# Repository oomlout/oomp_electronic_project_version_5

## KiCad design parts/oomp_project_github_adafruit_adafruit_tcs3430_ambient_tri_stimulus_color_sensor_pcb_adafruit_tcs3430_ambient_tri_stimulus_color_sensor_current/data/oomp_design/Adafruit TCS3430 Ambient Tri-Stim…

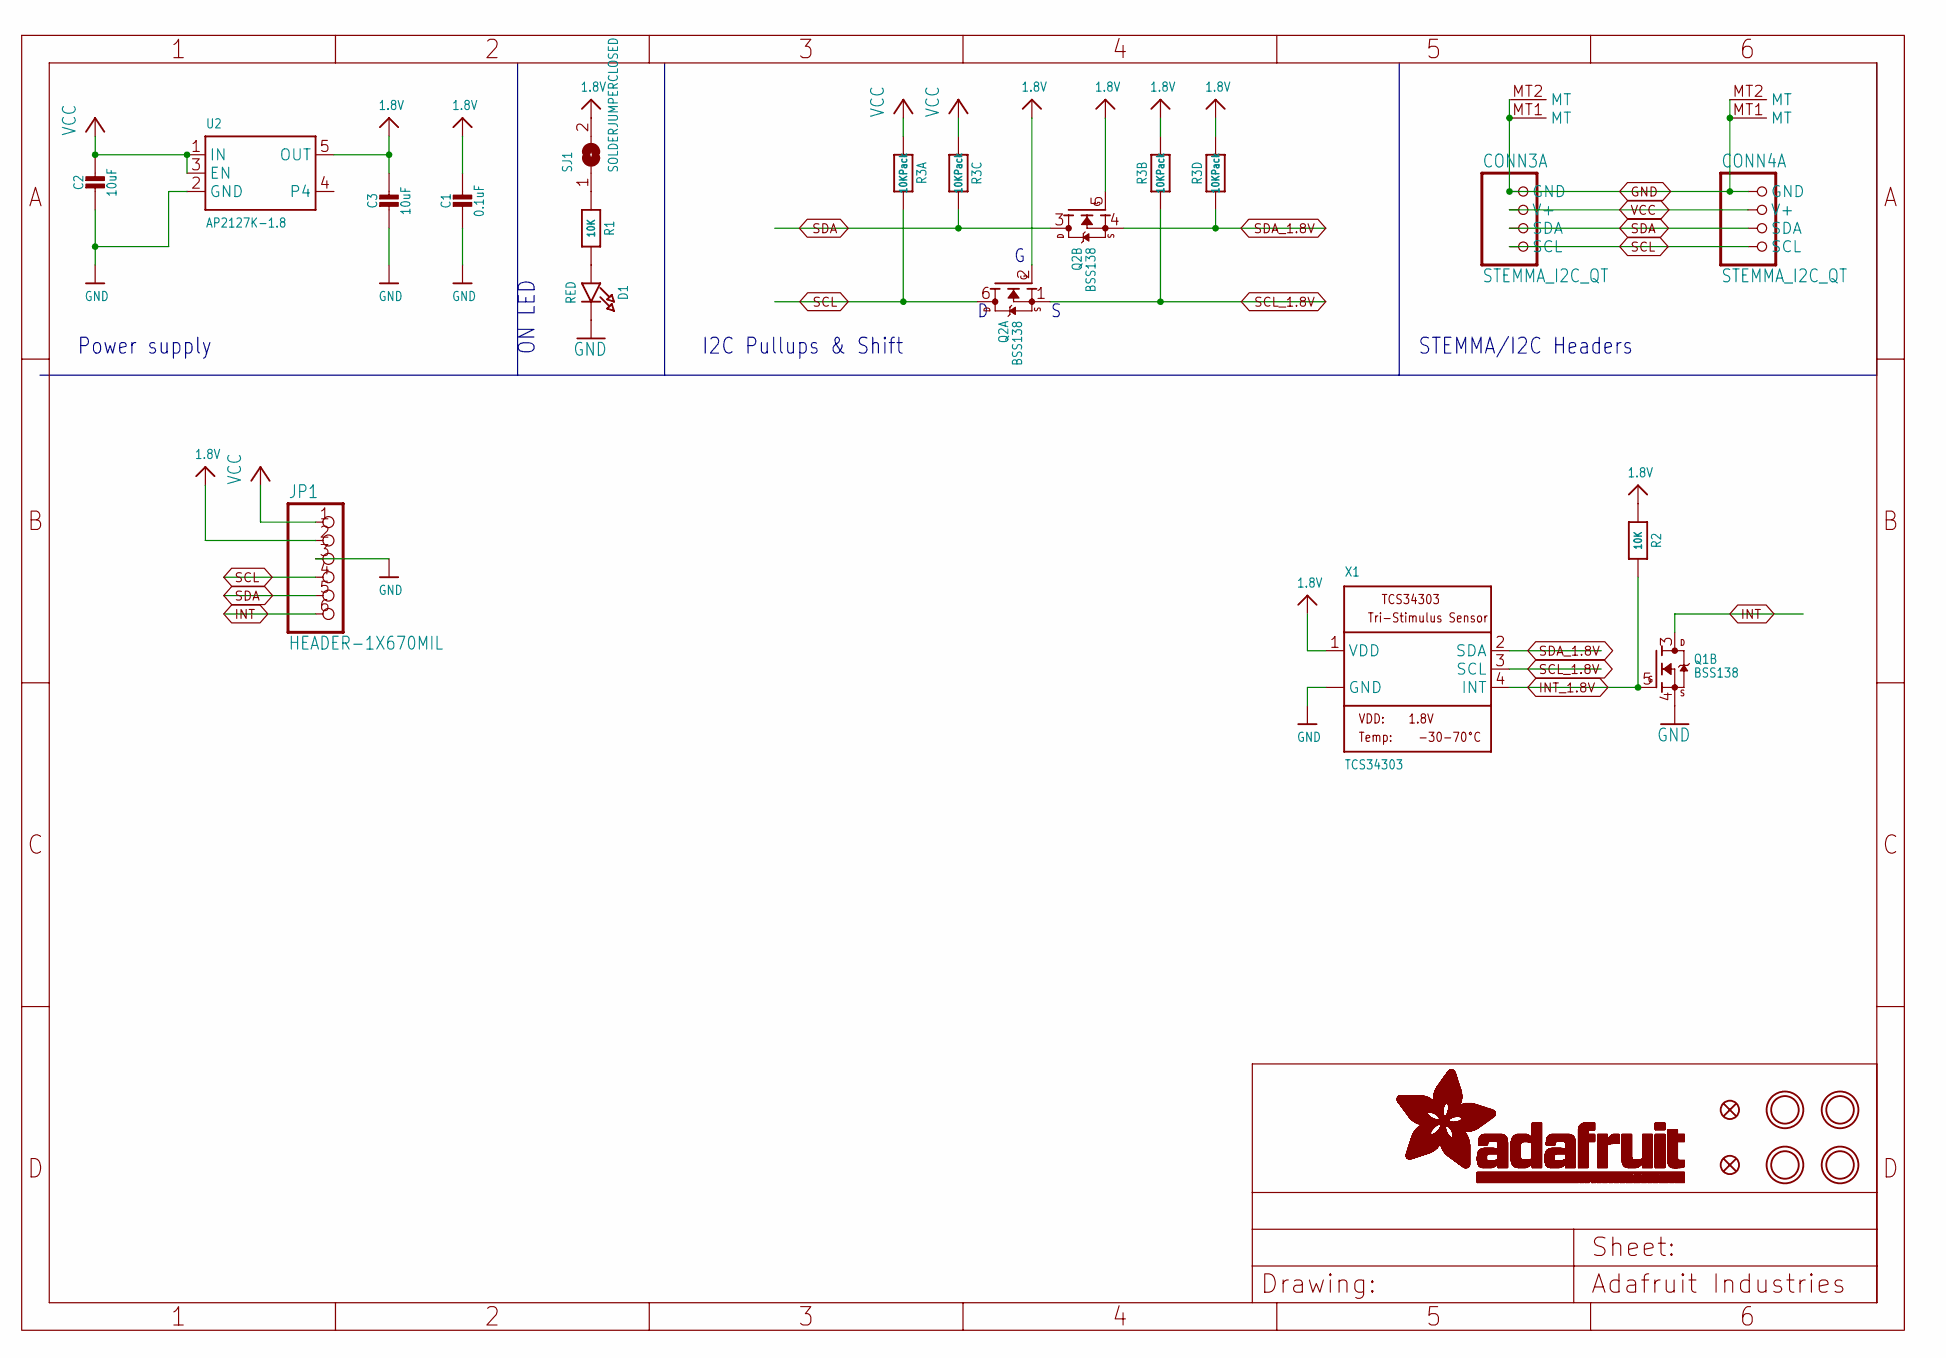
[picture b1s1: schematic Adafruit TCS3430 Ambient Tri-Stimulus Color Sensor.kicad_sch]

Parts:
C1: 0.1uF; 0603-NO
C2, C3: 10uF; 0805-NO
CONN3, CONN4: STEMMA_I2C_QT; JST_SH4; LCSC C2845363
D1: RED; CHIPLED_0603_NOOUTLINE; JLC_ROTATION 270
FID3, FID4: FIDUCIAL_0.5MM
JP1: HEADER-1X670MIL; 1X06_ROUND_70
Q1, Q2: BSS138; SOT363; JLC_ROTATION 270
R1, R2: 10K; 0603-NO
R3: 10KPack; RESPACK_4X0603
SJ1: SOLDERJUMPERCLOSED; SOLDERJUMPER_CLOSEDWIRE
U2: AP2127K-1.8; SOT23-5; JLC_ROTATION 270
U$1, U$9, U$17, U$20: MOUNTINGHOLE2.5; MOUNTINGHOLE_2.5_PLATED
X1: TCS34303

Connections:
1.8V: C1.1, C3.1, JP1.2, Q2.2 (G), Q2.5 (G), R2.1, R3.2 (1), R3.4 (1), SJ1.2, U2.5 (OUT), X1.1 (VDD)
GND: C1.2, C2.2, C3.2, CONN3.1 (GND), CONN3.MT1 (MT), CONN3.MT2 (MT), CONN4.1 (GND), CONN4.MT1 (MT), CONN4.MT2 (MT), D1.C, JP1.3, Q1.4 (S), U2.2 (GND), X1.7 (GND), X1.8 (GND)
INT: JP1.6, Q1.3 (D)
INT_1.8V: Q1.5 (G), R2.2, X1.4 (INT)
unnamed: D1.A, R1.2
unnamed: R1.1, SJ1.1
SCL: CONN3.4 (SCL), CONN4.4 (SCL), JP1.4, Q2.6 (D), R3.8 (2)
SCL_1.8V: Q2.1 (S), R3.7 (2), X1.3 (SCL)
SDA: CONN3.3 (SDA), CONN4.3 (SDA), JP1.5, Q2.3 (D), R3.6 (2)
SDA_1.8V: Q2.4 (S), R3.5 (2), X1.2 (SDA)
VCC: C2.1, CONN3.2 (V+), CONN4.2 (V+), JP1.1, R3.1, R3.3 (1), U2.1 (IN), U2.3 (EN)

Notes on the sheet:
Power supply
ON LED
STEMMA/I2C Headers
I2C Pullups & Shift

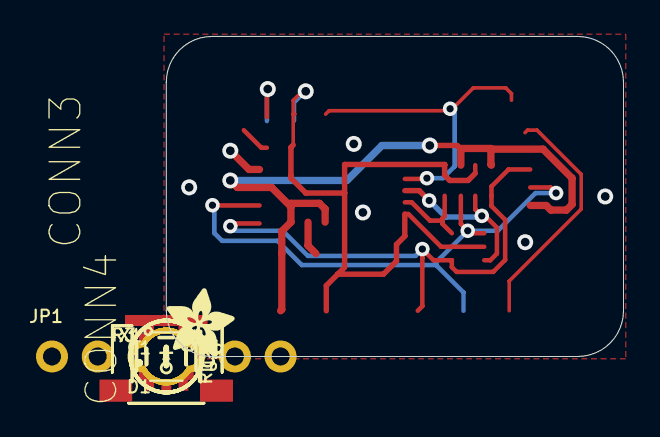
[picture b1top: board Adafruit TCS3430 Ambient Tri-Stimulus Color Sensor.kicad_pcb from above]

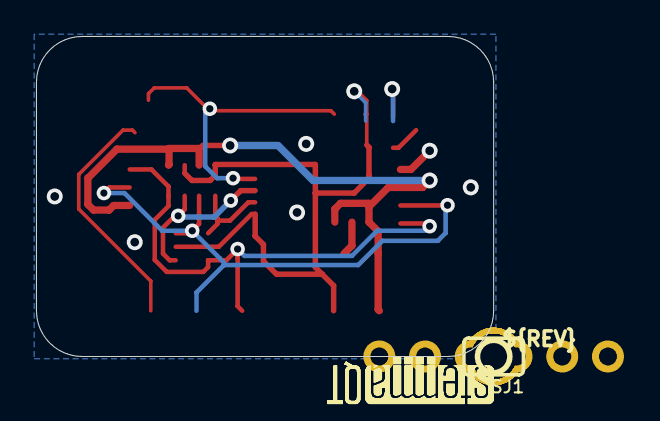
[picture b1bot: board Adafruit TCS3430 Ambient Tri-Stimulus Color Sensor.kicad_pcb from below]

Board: 2 copper layers, 25.4 x 17.8 mm, 39 parts (9 on the bottom side), 11 nets.

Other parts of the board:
PLABEL0: PLABEL0
PLABEL1: PLABEL1
PLABEL2: PLABEL2
PLABEL3: PLABEL3
PLABEL4: PLABEL4
PLABEL5: PLABEL5
PLABEL6: PLABEL6
PLABEL7: PLABEL7
PLABEL8: PLABEL8
PLABEL9: PLABEL9
PLABEL10: PLABEL10
PLABEL11: PLABEL11
PLABEL12: PLABEL12
PLABEL13: PLABEL13
U$22: ADAFRUIT_3.5MM
U$25: PCBFEAT-REV-040
U$30, U$31: STEMMAQT

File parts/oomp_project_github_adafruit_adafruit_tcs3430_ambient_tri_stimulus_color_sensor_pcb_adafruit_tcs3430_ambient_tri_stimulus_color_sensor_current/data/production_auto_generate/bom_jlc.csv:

Comment,Designator,Footprint,LCSC Part #
,JP1,1X06_ROUND_70,C37208
,U$22,ADAFRUIT_3.5MM,
,U$25,PCBFEAT-REV-040,
,PLABEL0,PLABEL0,
,PLABEL1,PLABEL1,
,PLABEL10,PLABEL10,
,PLABEL11,PLABEL11,
,PLABEL12,PLABEL12,
,PLABEL13,PLABEL13,
,PLABEL2,PLABEL2,
,PLABEL3,PLABEL3,
,PLABEL4,PLABEL4,
,PLABEL5,PLABEL5,
,PLABEL6,PLABEL6,
,PLABEL7,PLABEL7,
,PLABEL8,PLABEL8,
,PLABEL9,PLABEL9,
,"U$30,U$31",STEMMAQT,
0.1uF,C1,0603-NO,C14663
10K,"R1,R2",0603-NO,C98220
10KPack,R3,RESPACK_4X0603,C98220
10uF,"C2,C3",0805-NO,
AP2127K-1.8,U2,SOT23-5,
BSS138,"Q1,Q2",SOT363,
RED,D1,CHIPLED_0603_NOOUTLINE,
STEMMA_I2C_QT,"CONN3,CONN4",JST_SH4,C160404
TCS34303,X1,TCS34303,

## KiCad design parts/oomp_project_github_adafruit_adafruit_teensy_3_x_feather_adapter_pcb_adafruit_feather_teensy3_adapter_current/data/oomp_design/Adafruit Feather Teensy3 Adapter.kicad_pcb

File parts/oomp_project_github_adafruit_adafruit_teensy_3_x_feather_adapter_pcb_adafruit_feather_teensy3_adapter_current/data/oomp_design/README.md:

# OOMP KiCad design copy

Open `Adafruit Feather Teensy3 Adapter.kicad_pro` (or the `.kicad_pcb` / `.kicad_sch`) in KiCad. Local OOMP libraries are under `libraries/`. Original inputs are preserved in [../original/](../original/).

Only verified unchanged installed KiCad defaults were renamed. Modified, custom, unmatched and unavailable items remain unchanged. Soldering variants are never swapped during conversion. Existing pad coordinates, nets and UUIDs are preserved.

See [conversion_report.yaml](conversion_report.yaml) for every conversion and skip. Copy this directory before editing; regeneration refuses to overwrite edited design files.

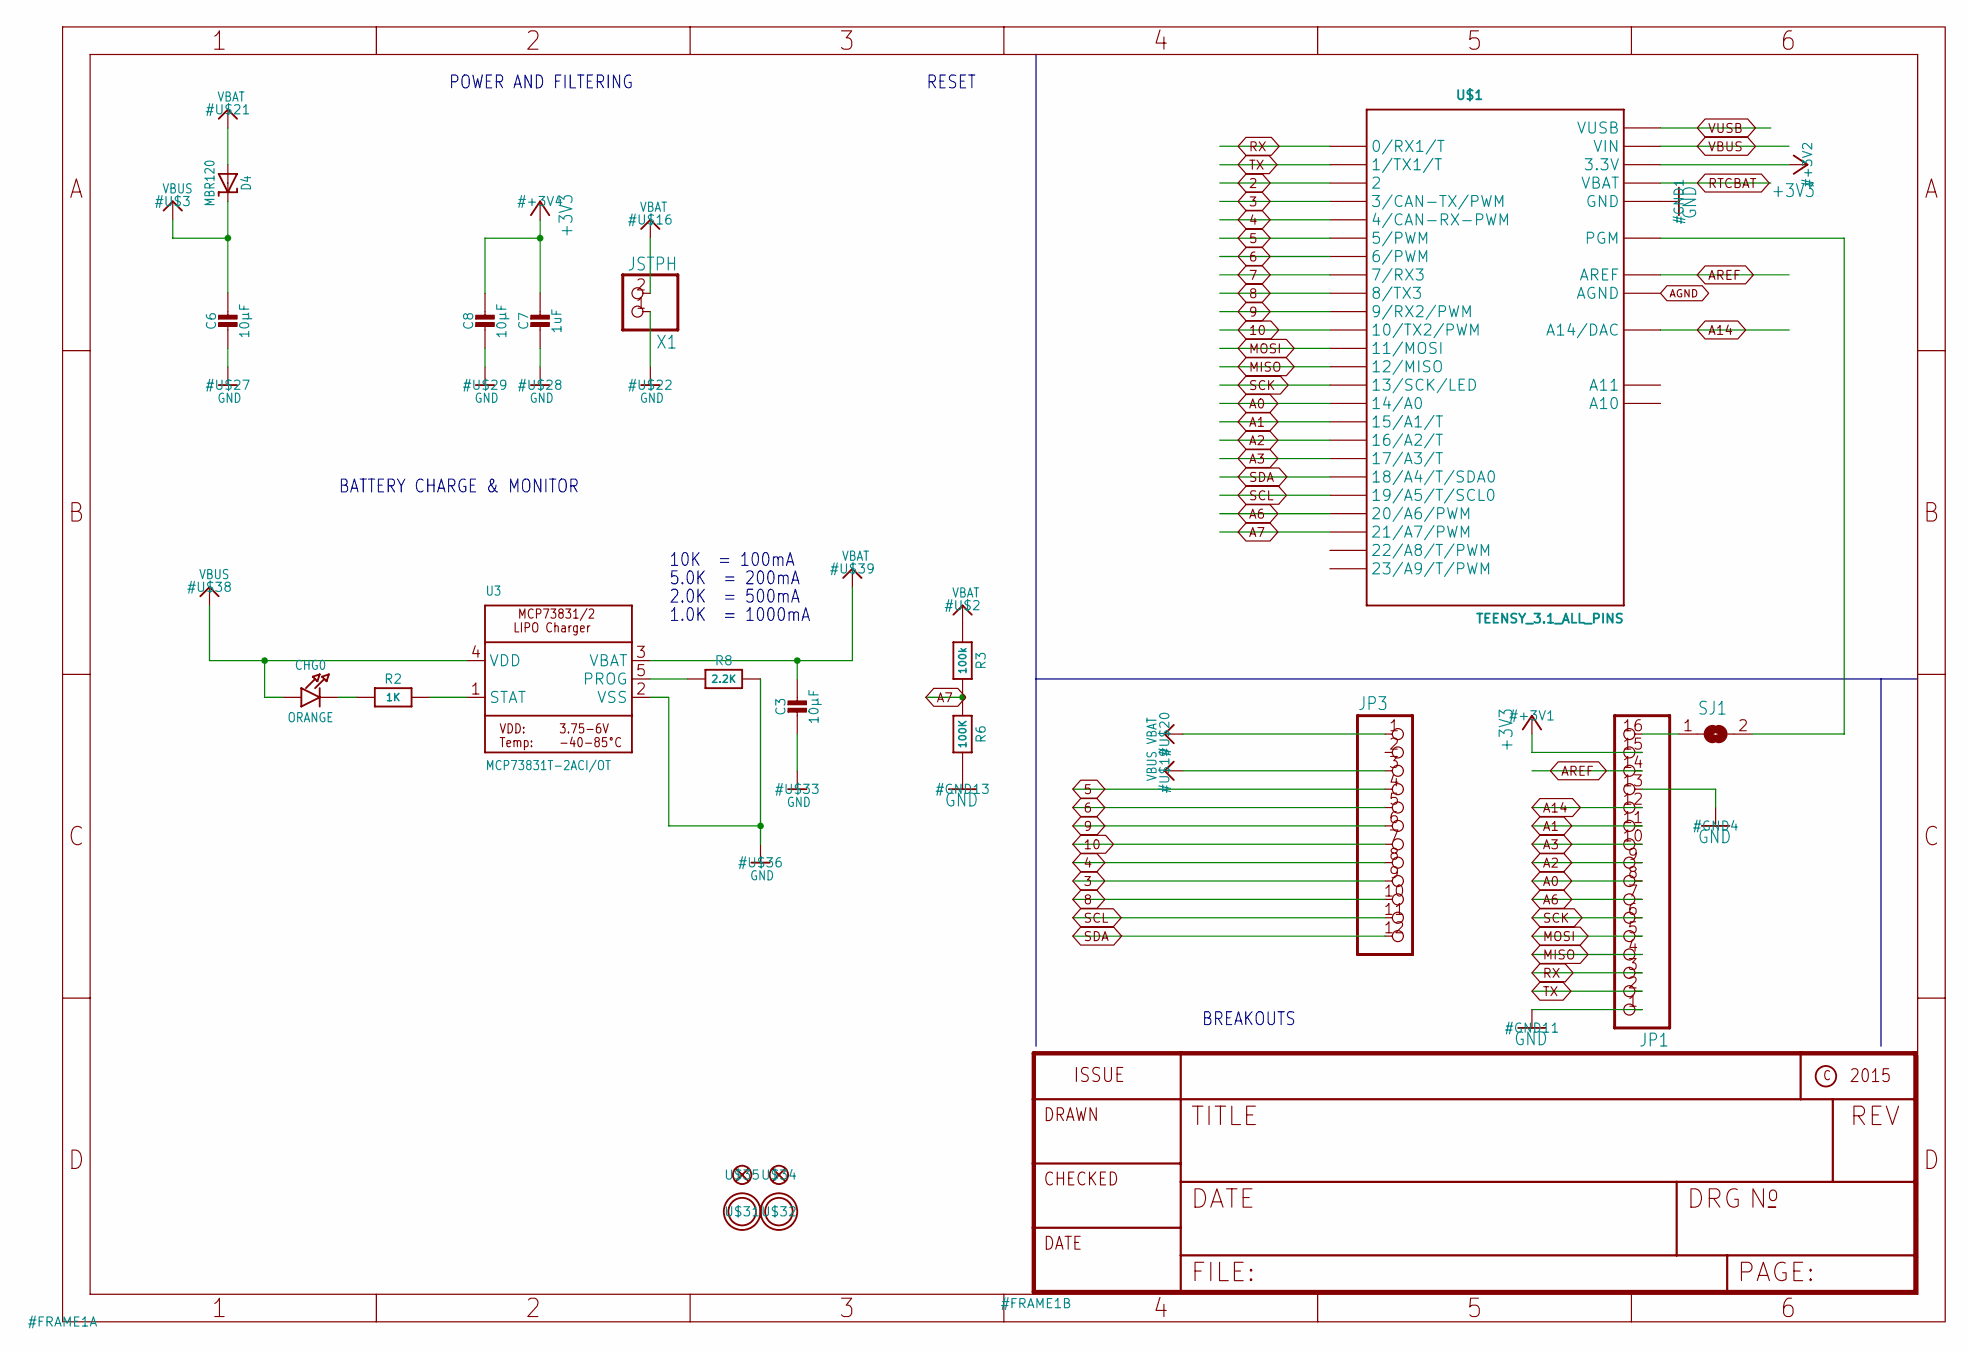
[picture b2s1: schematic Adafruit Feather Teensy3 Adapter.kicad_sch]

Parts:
C3, C6, C8: 10µF; 0805-NO
C7: 1uF; 0603-NO
CHG0: ORANGE; CHIPLED_0805_NOOUTLINE
D4: MBR120; SOD-123
JP1: HEADER-1X16ROUND; 1X16_ROUND
JP3: HEADER-1X12; 1X12_ROUND
R2: 1K; 0603-NO
R3: 100k; 0603-NO
R6: 100K; 0603-NO
R8: 2.2K; 0603-NO
SJ1: SOLDERJUMPERCLOSED; SOLDERJUMPER_CLOSEDWIRE
U3: MCP73831T-2ACI/OT; SOT23-5
U$1: TEENSY_3.1_ALL_PINS; TEENSY3-ALL_PINS
U$31, U$32: MOUNTINGHOLE2.5; MOUNTINGHOLE_2.5_PLATED
U$34, U$35: FIDUCIAL""; FIDUCIAL_1MM
X1: JSTPH; JSTPH2

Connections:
2: U$1.2
3: JP3.9, U$1.3 (3/CAN-TX/PWM)
4: JP3.8, U$1.4 (4/CAN-RX-PWM)
5: JP3.4, U$1.5 (5/PWM)
6: JP3.5, U$1.6 (6/PWM)
7: U$1.7 (7/RX3)
8: JP3.10, U$1.8 (8/TX3)
9: JP3.6, U$1.9 (9/RX2/PWM)
10: JP3.7, U$1.10 (10/TX2/PWM)
+3V3: C7.1, C8.1, JP1.15, U$1.3.3V, U$1.3.3V1 (3.3V)
A0: JP1.8, U$1.14/A0
A1: JP1.11, U$1.15/A1 (15/A1/T)
A2: JP1.9, U$1.16/A2 (16/A2/T)
A3: JP1.10, U$1.17/A3 (17/A3/T)
A6: JP1.7, U$1.20/A6 (20/A6/PWM)
A7: R3.2, R6.1, U$1.21/A7 (21/A7/PWM)
A14: JP1.12, U$1.RESET/DAC (A14/DAC)
AGND: U$1.AGND
AREF: JP1.14, U$1.AREF
BOOT: SJ1.2, U$1.PGM
GND: C3.2, C6.2, C7.2, C8.2, JP1.1, JP1.13, R6.2, R8.2, U3.2 (VSS), U$1.GND, U$1.GND1 (GND), X1.1
MISO: JP1.4, U$1.12 (12/MISO)
MOSI: JP1.5, U$1.11 (11/MOSI)
unnamed: CHG0.C, R2.1
unnamed: R2.2, U3.1 (STAT)
unnamed: R8.1, U3.5 (PROG)
RST/BOOT: JP1.16, SJ1.1
RTCBAT: U$1.VBAT
RX: JP1.3, U$1.0 (0/RX1/T)
SCK: JP1.6, U$1.13 (13/SCK/LED)
SCL: JP3.11, U$1.19/A5 (19/A5/T/SCL0)
SDA: JP3.12, U$1.18/A4 (18/A4/T/SDA0)
TX: JP1.2, U$1.1 (1/TX1/T)
VBAT: C3.1, D4.A, JP3.1, R3.1, U3.3 (VBAT), X1.2
VBUS: C6.1, CHG0.A, D4.C, JP3.3, U3.4 (VDD), U$1.VIN
VUSB: U$1.VUSB

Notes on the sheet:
POWER AND FILTERING
RESET
2.0K = 500mA
10K = 100mA
1.0K = 1000mA
BATTERY CHARGE & MONITOR
5.0K = 200mA
BREAKOUTS

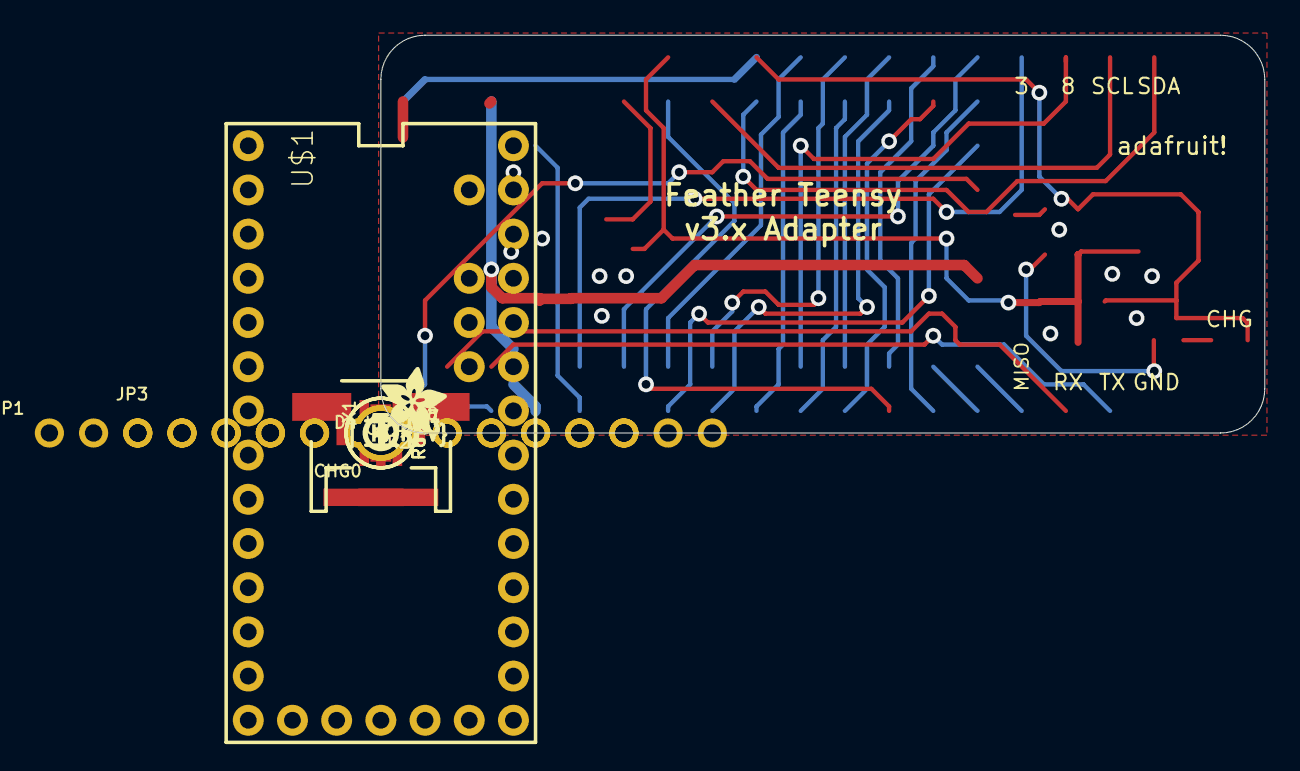
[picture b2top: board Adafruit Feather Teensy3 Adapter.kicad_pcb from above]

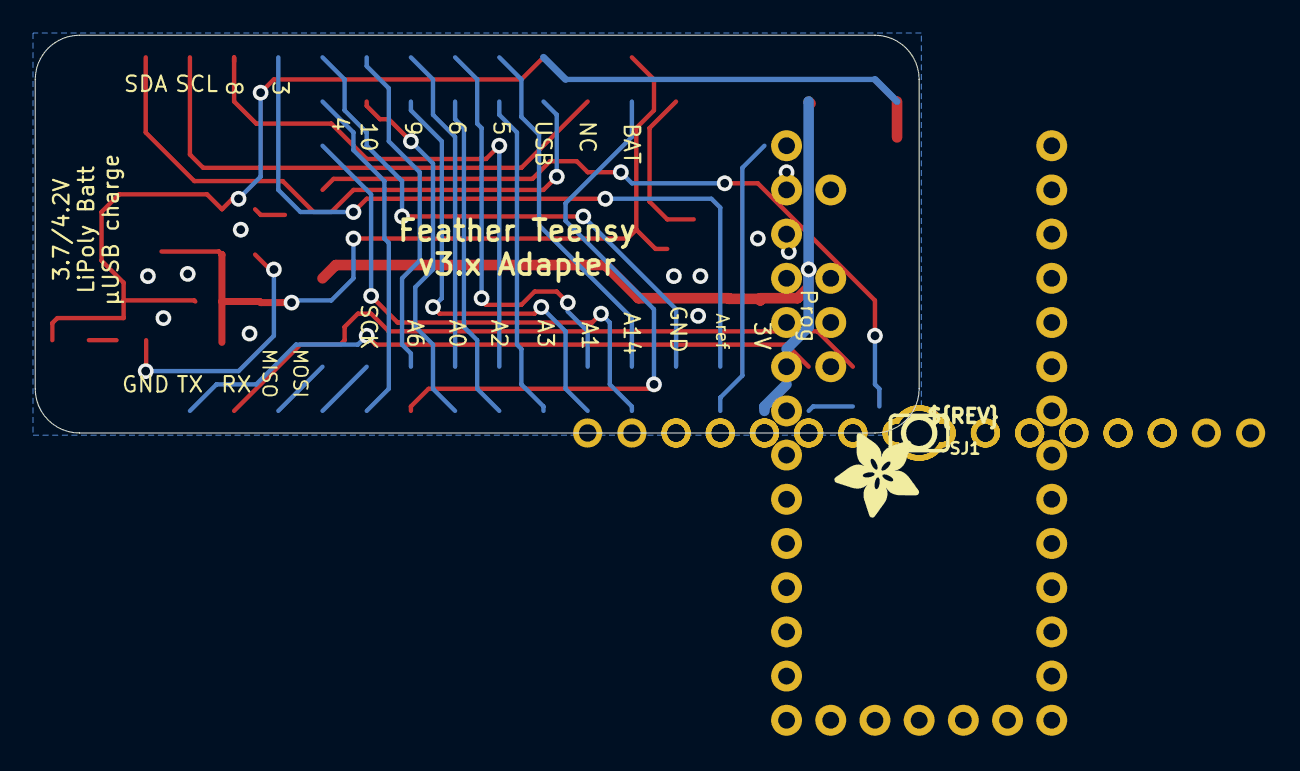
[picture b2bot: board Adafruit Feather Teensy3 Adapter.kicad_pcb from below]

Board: 2 copper layers, 50.8 x 22.9 mm, 24 parts (3 on the bottom side), 31 nets.

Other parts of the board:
U$4: ADAFRUIT_5MM
U$5, U$6: PCBFEAT-REV-040
U$7: ADAFRUIT_3.5MM

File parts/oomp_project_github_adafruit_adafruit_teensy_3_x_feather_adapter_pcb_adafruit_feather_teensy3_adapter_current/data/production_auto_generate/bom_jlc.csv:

Comment,Designator,Footprint,LCSC Part #
,JP3,Adafruit Feather Teensy3 Adapter-import-fps:1X12_ROUND,C7501588
,JP1,Adafruit Feather Teensy3 Adapter-import-fps:1X16_ROUND,C7501270
,U$7,Adafruit Feather Teensy3 Adapter-import-fps:ADAFRUIT_3.5MM,
,U$4,Adafruit Feather Teensy3 Adapter-import-fps:ADAFRUIT_5MM,
,"U$5,U$6",Adafruit Feather Teensy3 Adapter-import-fps:PCBFEAT-REV-040,
100k,R3,Adafruit Feather Teensy3 Adapter-import-fps:0603-NO,C25803
100K,R6,Adafruit Feather Teensy3 Adapter-import-fps:0603-NO,C25803
10µF,"C3,C6,C8",Adafruit Feather Teensy3 Adapter-import-fps:0805-NO,
1K,R2,Adafruit Feather Teensy3 Adapter-import-fps:0603-NO,C2907002
1uF,C7,Adafruit Feather Teensy3 Adapter-import-fps:0603-NO,C5673
2.2K,R8,Adafruit Feather Teensy3 Adapter-import-fps:0603-NO,C4190
"FIDUCIAL""""","U$34,U$35",Adafruit Feather Teensy3 Adapter-import-fps:FIDUCIAL_1MM,
JSTPH,X1,Adafruit Feather Teensy3 Adapter-import-fps:JSTPH2,
MBR120,D4,Adafruit Feather Teensy3 Adapter-import-fps:SOD-123,
MCP73831T-2ACI/OT,U3,Adafruit Feather Teensy3 Adapter-import-fps:SOT23-5,
ORANGE,CHG0,Adafruit Feather Teensy3 Adapter-import-fps:CHIPLED_0805_NOOUTLINE,
TEENSY_3.1_ALL_PINS,U$1,Adafruit Feather Teensy3 Adapter-import-fps:TEENSY3-ALL_PINS,

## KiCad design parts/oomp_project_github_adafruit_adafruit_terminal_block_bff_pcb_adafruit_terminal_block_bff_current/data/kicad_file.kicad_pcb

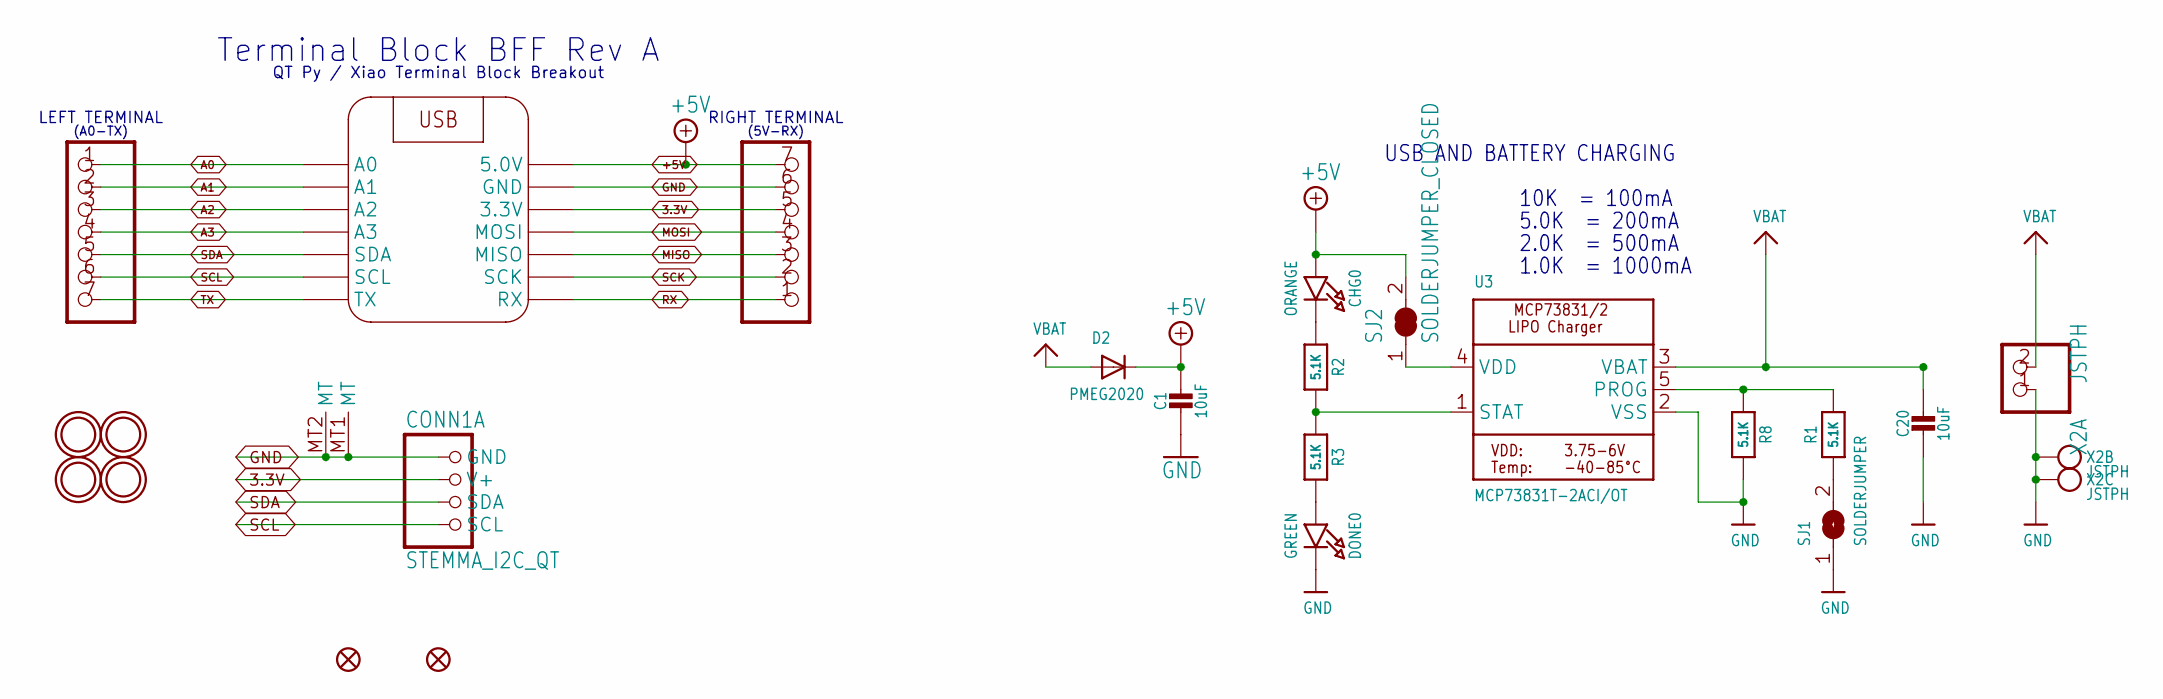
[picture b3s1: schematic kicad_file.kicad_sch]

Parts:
C1, C20: 10uF; 0805-NO
CHG0: ORANGE; CHIPLED_0603_NOOUTLINE
CONN1: STEMMA_I2C_QT; JST_SH4; LCSC C2845363
D2: PMEG2020; SOD-123FL
DONE0: GREEN; CHIPLED_0603_NOOUTLINE
FID1, FID2: FIDUCIAL_0.5MM
JP1, JP2: Terminal; 1X07_2.54MMTERMINAL
R1, R2, R3, R8: 5.1K; _0402NO
SJ1: SOLDERJUMPER; SOLDERJUMPER_ARROW_NOPASTE
SJ2: SOLDERJUMPER_CLOSED; SOLDERJUMPER_CLOSEDWIRE
U3: MCP73831T-2ACI/OT; SOT23-5; JLC_ROTATION 270
U$1, U$2, U$3, U$4: MOUNTINGHOLE2.5; MOUNTINGHOLE_2.5_PLATED
X1: QTPY_SOCKET_DUAL_SMT; QTPY_SMT
X2: JSTPH; JSTPH2_BATT; LCSC C47647

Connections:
3.3V: CONN1.2 (V+), JP1.5, X1.12 (3.3V), X1.12B (3.3V)
+5V: C1.1, CHG0.A, D2.C, JP1.7, SJ2.2, X1.14 (5.0V), X1.14B (5.0V)
A0: JP2.1, X1.1 (A0), X1.1B (A0)
A1: JP2.2, X1.2 (A1), X1.2B (A1)
A2: JP2.3, X1.3 (A2), X1.3B (A2)
A3: JP2.4, X1.4 (A3), X1.4B (A3)
GND: C1.2, C20.2, CONN1.1 (GND), CONN1.MT1 (MT), CONN1.MT2 (MT), DONE0.C, JP1.6, R8.2, SJ1.1, U3.2 (VSS), X1.13 (GND), X1.13B (GND), X2.1, X2.NC1, X2.NC2
MISO: JP1.3, X1.10 (MISO), X1.10B (MISO)
MOSI: JP1.4, X1.11 (MOSI), X1.11B (MOSI)
unnamed: R1.1, SJ1.2
unnamed: CHG0.C, R2.1
unnamed: R2.2, R3.1, U3.1 (STAT)
unnamed: R1.2, R8.1, U3.5 (PROG)
unnamed: DONE0.A, R3.2
unnamed: SJ2.1, U3.4 (VDD)
RX: JP1.1, X1.8 (RX), X1.8B (RX)
SCK: JP1.2, X1.9 (SCK), X1.9B (SCK)
SCL: CONN1.4 (SCL), JP2.6, X1.6 (SCL), X1.6B (SCL)
SDA: CONN1.3 (SDA), JP2.5, X1.5 (SDA), X1.5B (SDA)
TX: JP2.7, X1.7 (TX), X1.7B (TX)
VBAT: C20.1, D2.A, U3.3 (VBAT), X2.2

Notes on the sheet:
5.0K = 200mA
LEFT TERMINAL
1.0K = 1000mA
(A0-TX)
2.0K = 500mA
RIGHT TERMINAL
USB AND BATTERY CHARGING
(5V-RX)
Terminal Block BFF Rev A
10K = 100mA
QT Py / Xiao Terminal Block Breakout

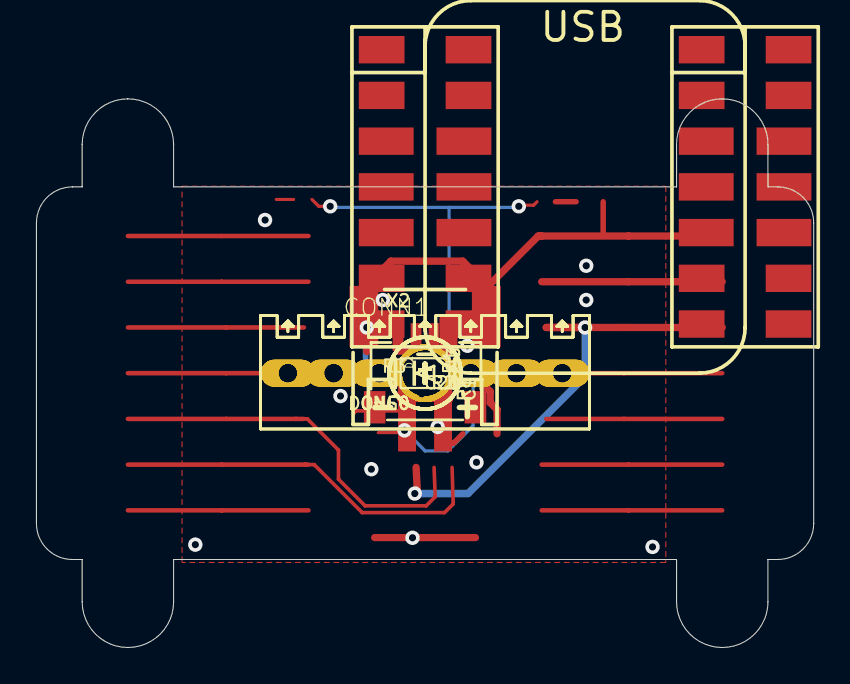
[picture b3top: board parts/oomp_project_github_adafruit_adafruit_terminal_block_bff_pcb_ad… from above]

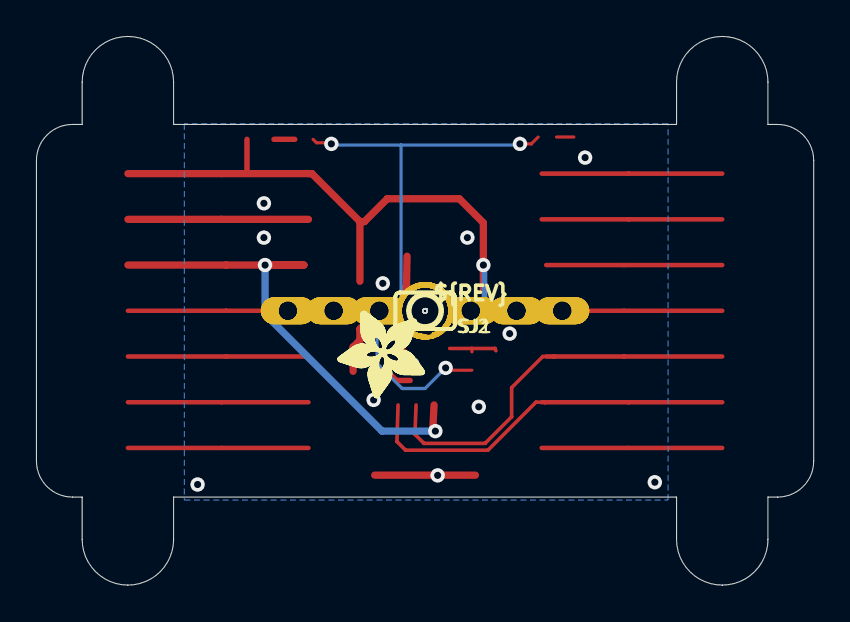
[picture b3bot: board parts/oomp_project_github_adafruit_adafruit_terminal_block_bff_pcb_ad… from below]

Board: 16 copper layers, 43.2 x 30.5 mm, 96 parts (26 on the bottom side), 21 nets.

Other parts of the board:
PLABEL0: PLABEL0
PLABEL1: PLABEL1
PLABEL2: PLABEL2
PLABEL3: PLABEL3
PLABEL4: PLABEL4
PLABEL5: PLABEL5
PLABEL6: PLABEL6
PLABEL7: PLABEL7
PLABEL8: PLABEL8
PLABEL9: PLABEL9
PLABEL10: PLABEL10
PLABEL11: PLABEL11
PLABEL12: PLABEL12
PLABEL13: PLABEL13
PLABEL14: PLABEL14
PLABEL15: PLABEL15
PLABEL16: PLABEL16
PLABEL17: PLABEL17
PLABEL18: PLABEL18
PLABEL19: PLABEL19
PLABEL20: PLABEL20
PLABEL21: PLABEL21
PLABEL22: PLABEL22
PLABEL23: PLABEL23
PLABEL24: PLABEL24
PLABEL25: PLABEL25
PLABEL26: PLABEL26
PLABEL27: PLABEL27
PLABEL28: PLABEL28
PLABEL29: PLABEL29
PLABEL31: PLABEL31
PLABEL32: PLABEL32
PLABEL33: PLABEL33
PLABEL34: PLABEL34
PLABEL35: PLABEL35
PLABEL36: PLABEL36
PLABEL37: PLABEL37
PLABEL38: PLABEL38
U$7, U$8: ADAFRUIT_5MM
U$9: PCBFEAT-REV-040
UNK_HOLE_0: dummyfp0
UNK_HOLE_1: dummyfp1
UNK_HOLE_2: dummyfp2
UNK_HOLE_3: dummyfp3
UNK_HOLE_4: dummyfp4
UNK_HOLE_5: dummyfp5
UNK_HOLE_6: dummyfp6
UNK_HOLE_7: dummyfp7
UNK_HOLE_8: dummyfp8
UNK_HOLE_9: dummyfp9
UNK_HOLE_10: dummyfp10
UNK_HOLE_11: dummyfp11
UNK_HOLE_12: dummyfp12
UNK_HOLE_13: dummyfp13
UNK_HOLE_14: dummyfp14
UNK_HOLE_15: dummyfp15
UNK_HOLE_16: dummyfp16
UNK_HOLE_17: dummyfp17
UNK_HOLE_18: dummyfp18
UNK_HOLE_19: dummyfp19
UNK_HOLE_20: dummyfp20
UNK_HOLE_21: dummyfp21
UNK_HOLE_22: dummyfp22
UNK_HOLE_23: dummyfp23
UNK_HOLE_24: dummyfp24
UNK_HOLE_25: dummyfp25
UNK_HOLE_26: dummyfp26
UNK_HOLE_27: dummyfp27
UNK_HOLE_28: dummyfp28
UNK_HOLE_29: dummyfp29
UNK_HOLE_30: dummyfp30
UNK_HOLE_31: dummyfp31

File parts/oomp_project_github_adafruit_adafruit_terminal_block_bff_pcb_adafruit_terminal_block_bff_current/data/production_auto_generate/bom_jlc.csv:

Comment,Designator,Footprint,LCSC Part #
,"U$7,U$8",Adafruit Terminal Block BFF-import-fps:ADAFRUIT_5MM,
,U$9,Adafruit Terminal Block BFF-import-fps:PCBFEAT-REV-040,
,PLABEL0,Adafruit Terminal Block BFF-import-fps:PLABEL0,
,PLABEL1,Adafruit Terminal Block BFF-import-fps:PLABEL1,
,PLABEL10,Adafruit Terminal Block BFF-import-fps:PLABEL10,
,PLABEL11,Adafruit Terminal Block BFF-import-fps:PLABEL11,
,PLABEL12,Adafruit Terminal Block BFF-import-fps:PLABEL12,
,PLABEL13,Adafruit Terminal Block BFF-import-fps:PLABEL13,
,PLABEL14,Adafruit Terminal Block BFF-import-fps:PLABEL14,
,PLABEL15,Adafruit Terminal Block BFF-import-fps:PLABEL15,
,PLABEL16,Adafruit Terminal Block BFF-import-fps:PLABEL16,
,PLABEL17,Adafruit Terminal Block BFF-import-fps:PLABEL17,
,PLABEL18,Adafruit Terminal Block BFF-import-fps:PLABEL18,
,PLABEL19,Adafruit Terminal Block BFF-import-fps:PLABEL19,
,PLABEL2,Adafruit Terminal Block BFF-import-fps:PLABEL2,
,PLABEL20,Adafruit Terminal Block BFF-import-fps:PLABEL20,
,PLABEL21,Adafruit Terminal Block BFF-import-fps:PLABEL21,
,PLABEL22,Adafruit Terminal Block BFF-import-fps:PLABEL22,
,PLABEL23,Adafruit Terminal Block BFF-import-fps:PLABEL23,
,PLABEL24,Adafruit Terminal Block BFF-import-fps:PLABEL24,
,PLABEL25,Adafruit Terminal Block BFF-import-fps:PLABEL25,
,PLABEL26,Adafruit Terminal Block BFF-import-fps:PLABEL26,
,PLABEL27,Adafruit Terminal Block BFF-import-fps:PLABEL27,
,PLABEL28,Adafruit Terminal Block BFF-import-fps:PLABEL28,
,PLABEL29,Adafruit Terminal Block BFF-import-fps:PLABEL29,
,PLABEL3,Adafruit Terminal Block BFF-import-fps:PLABEL3,
,PLABEL31,Adafruit Terminal Block BFF-import-fps:PLABEL31,
,PLABEL32,Adafruit Terminal Block BFF-import-fps:PLABEL32,
,PLABEL33,Adafruit Terminal Block BFF-import-fps:PLABEL33,
,PLABEL34,Adafruit Terminal Block BFF-import-fps:PLABEL34,
,PLABEL35,Adafruit Terminal Block BFF-import-fps:PLABEL35,
,PLABEL36,Adafruit Terminal Block BFF-import-fps:PLABEL36,
,PLABEL37,Adafruit Terminal Block BFF-import-fps:PLABEL37,
,PLABEL38,Adafruit Terminal Block BFF-import-fps:PLABEL38,
,PLABEL4,Adafruit Terminal Block BFF-import-fps:PLABEL4,
,PLABEL5,Adafruit Terminal Block BFF-import-fps:PLABEL5,
,PLABEL6,Adafruit Terminal Block BFF-import-fps:PLABEL6,
,PLABEL7,Adafruit Terminal Block BFF-import-fps:PLABEL7,
,PLABEL8,Adafruit Terminal Block BFF-import-fps:PLABEL8,
,PLABEL9,Adafruit Terminal Block BFF-import-fps:PLABEL9,
10uF,"C1,C20",Adafruit Terminal Block BFF-import-fps:0805-NO,
5.1K,"R1,R2,R3,R8",Adafruit Terminal Block BFF-import-fps:_0402NO,C25905
GREEN,DONE0,Adafruit Terminal Block BFF-import-fps:CHIPLED_0603_NOOUTLINE,
JSTPH,X2,Adafruit Terminal Block BFF-import-fps:JSTPH2_BATT,
MCP73831T-2ACI/OT,U3,Adafruit Terminal Block BFF-import-fps:SOT23-5,
ORANGE,CHG0,Adafruit Terminal Block BFF-import-fps:CHIPLED_0603_NOOUTLINE,
PMEG2020,D2,Adafruit Terminal Block BFF-import-fps:SOD-123FL,
QTPY_SOCKET_DUAL_SMT,X1,Adafruit Terminal Block BFF-import-fps:QTPY_SMT,
STEMMA_I2C_QT,CONN1,Adafruit Terminal Block BFF-import-fps:JST_SH4,C160404
Terminal,"JP1,JP2",Adafruit Terminal Block BFF-import-fps:1X07_2.54MMTERMINAL,C7501585
